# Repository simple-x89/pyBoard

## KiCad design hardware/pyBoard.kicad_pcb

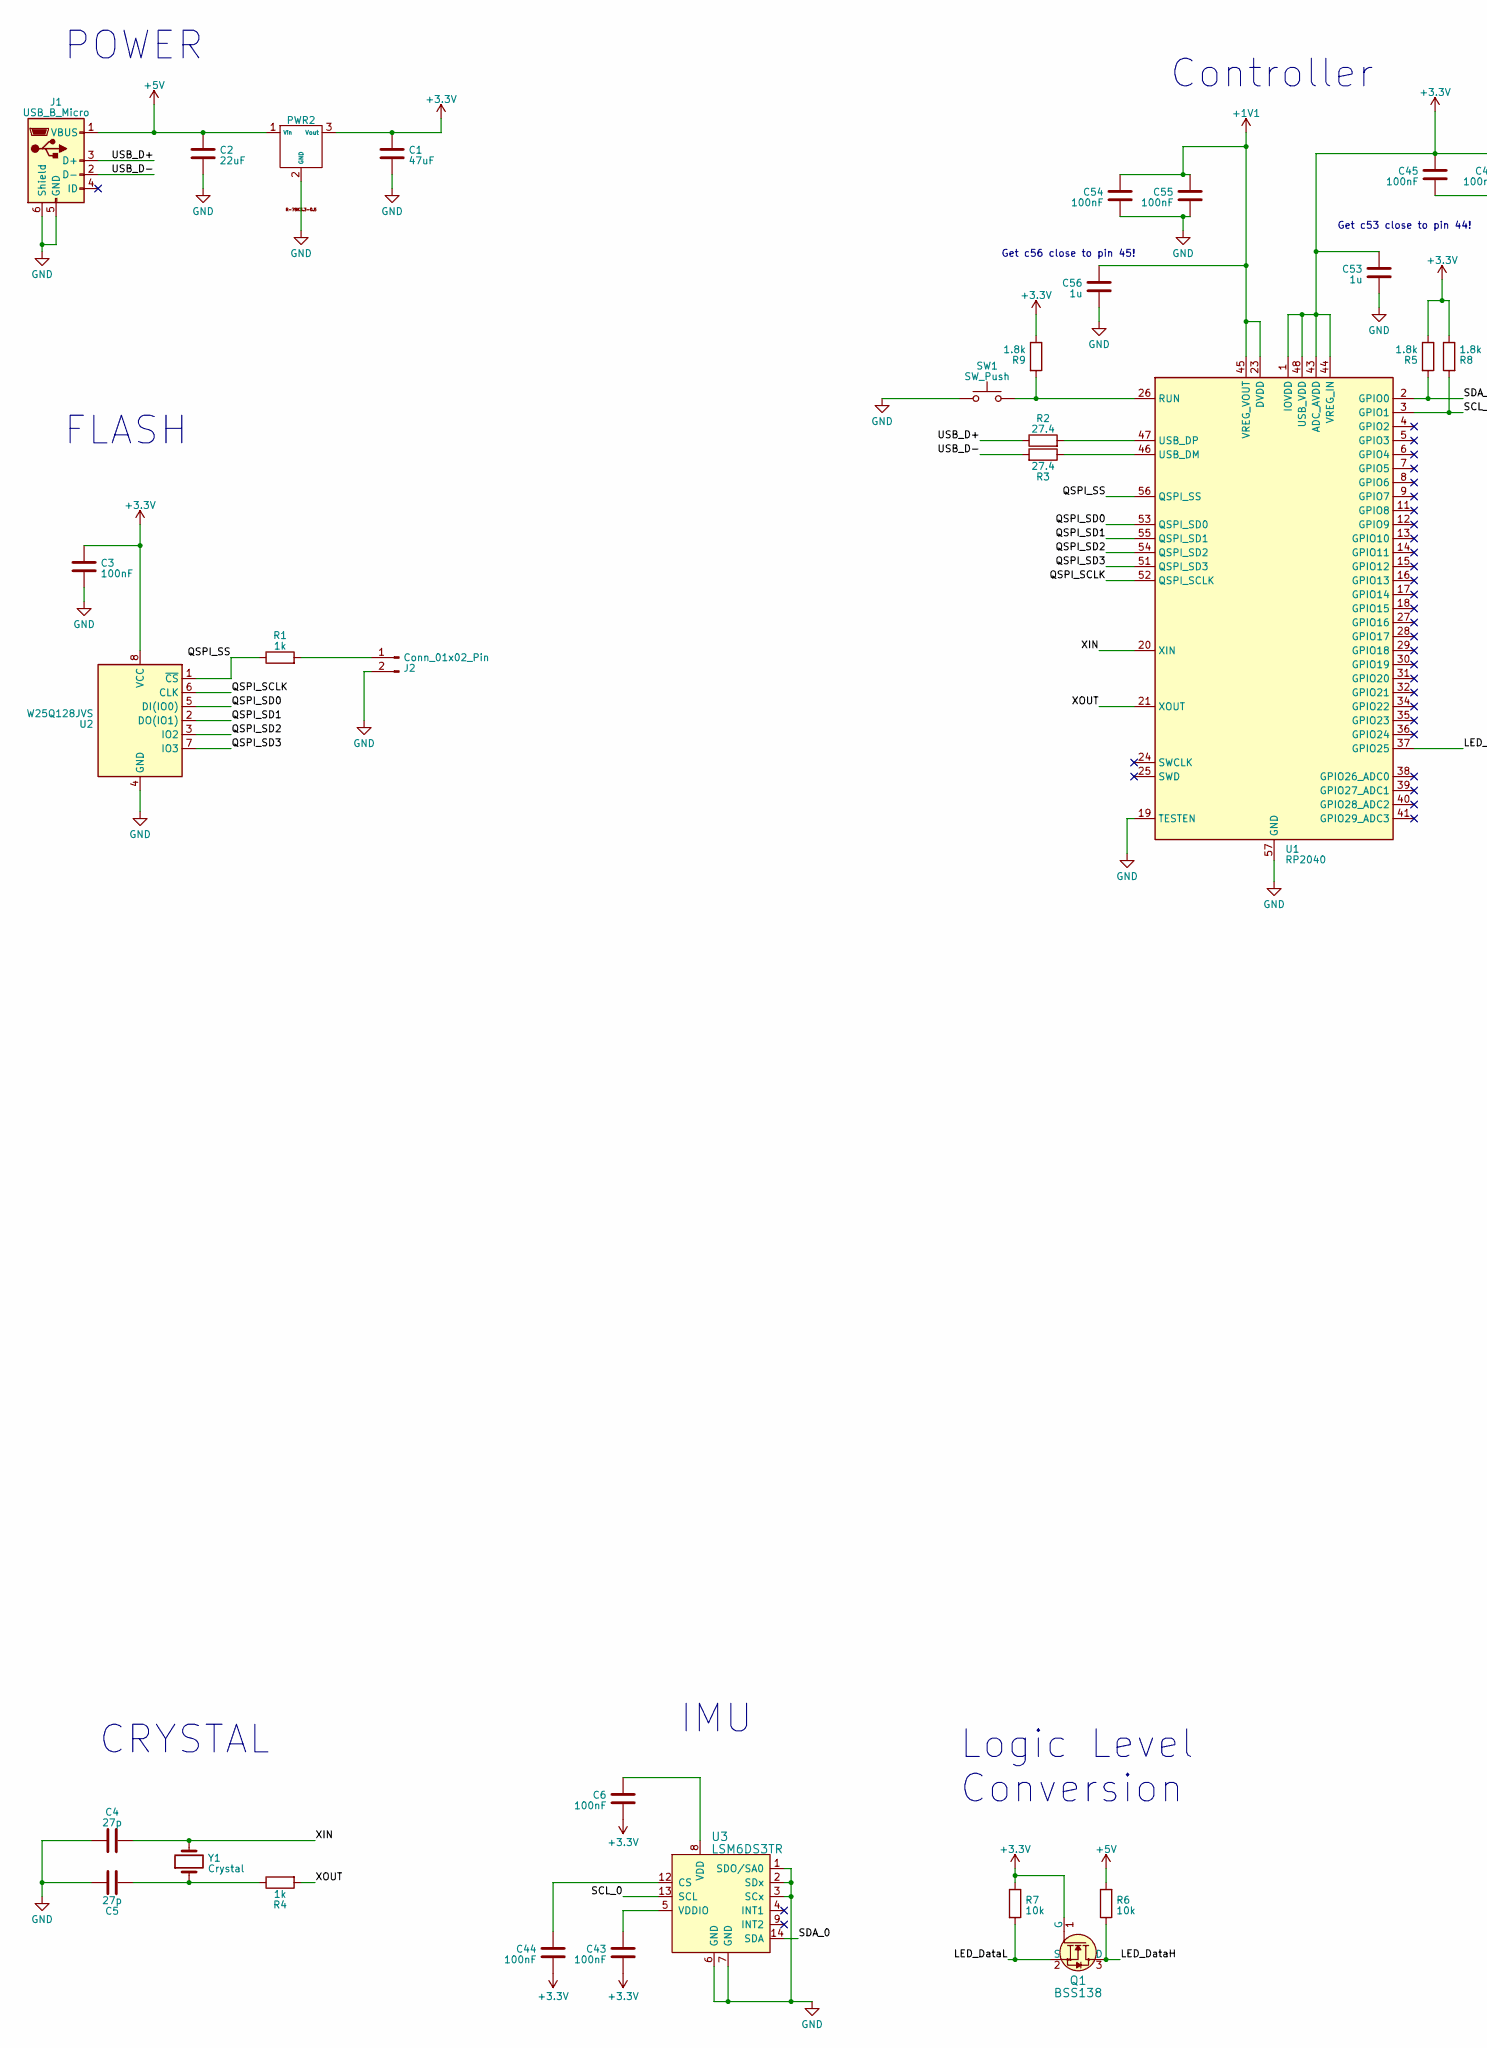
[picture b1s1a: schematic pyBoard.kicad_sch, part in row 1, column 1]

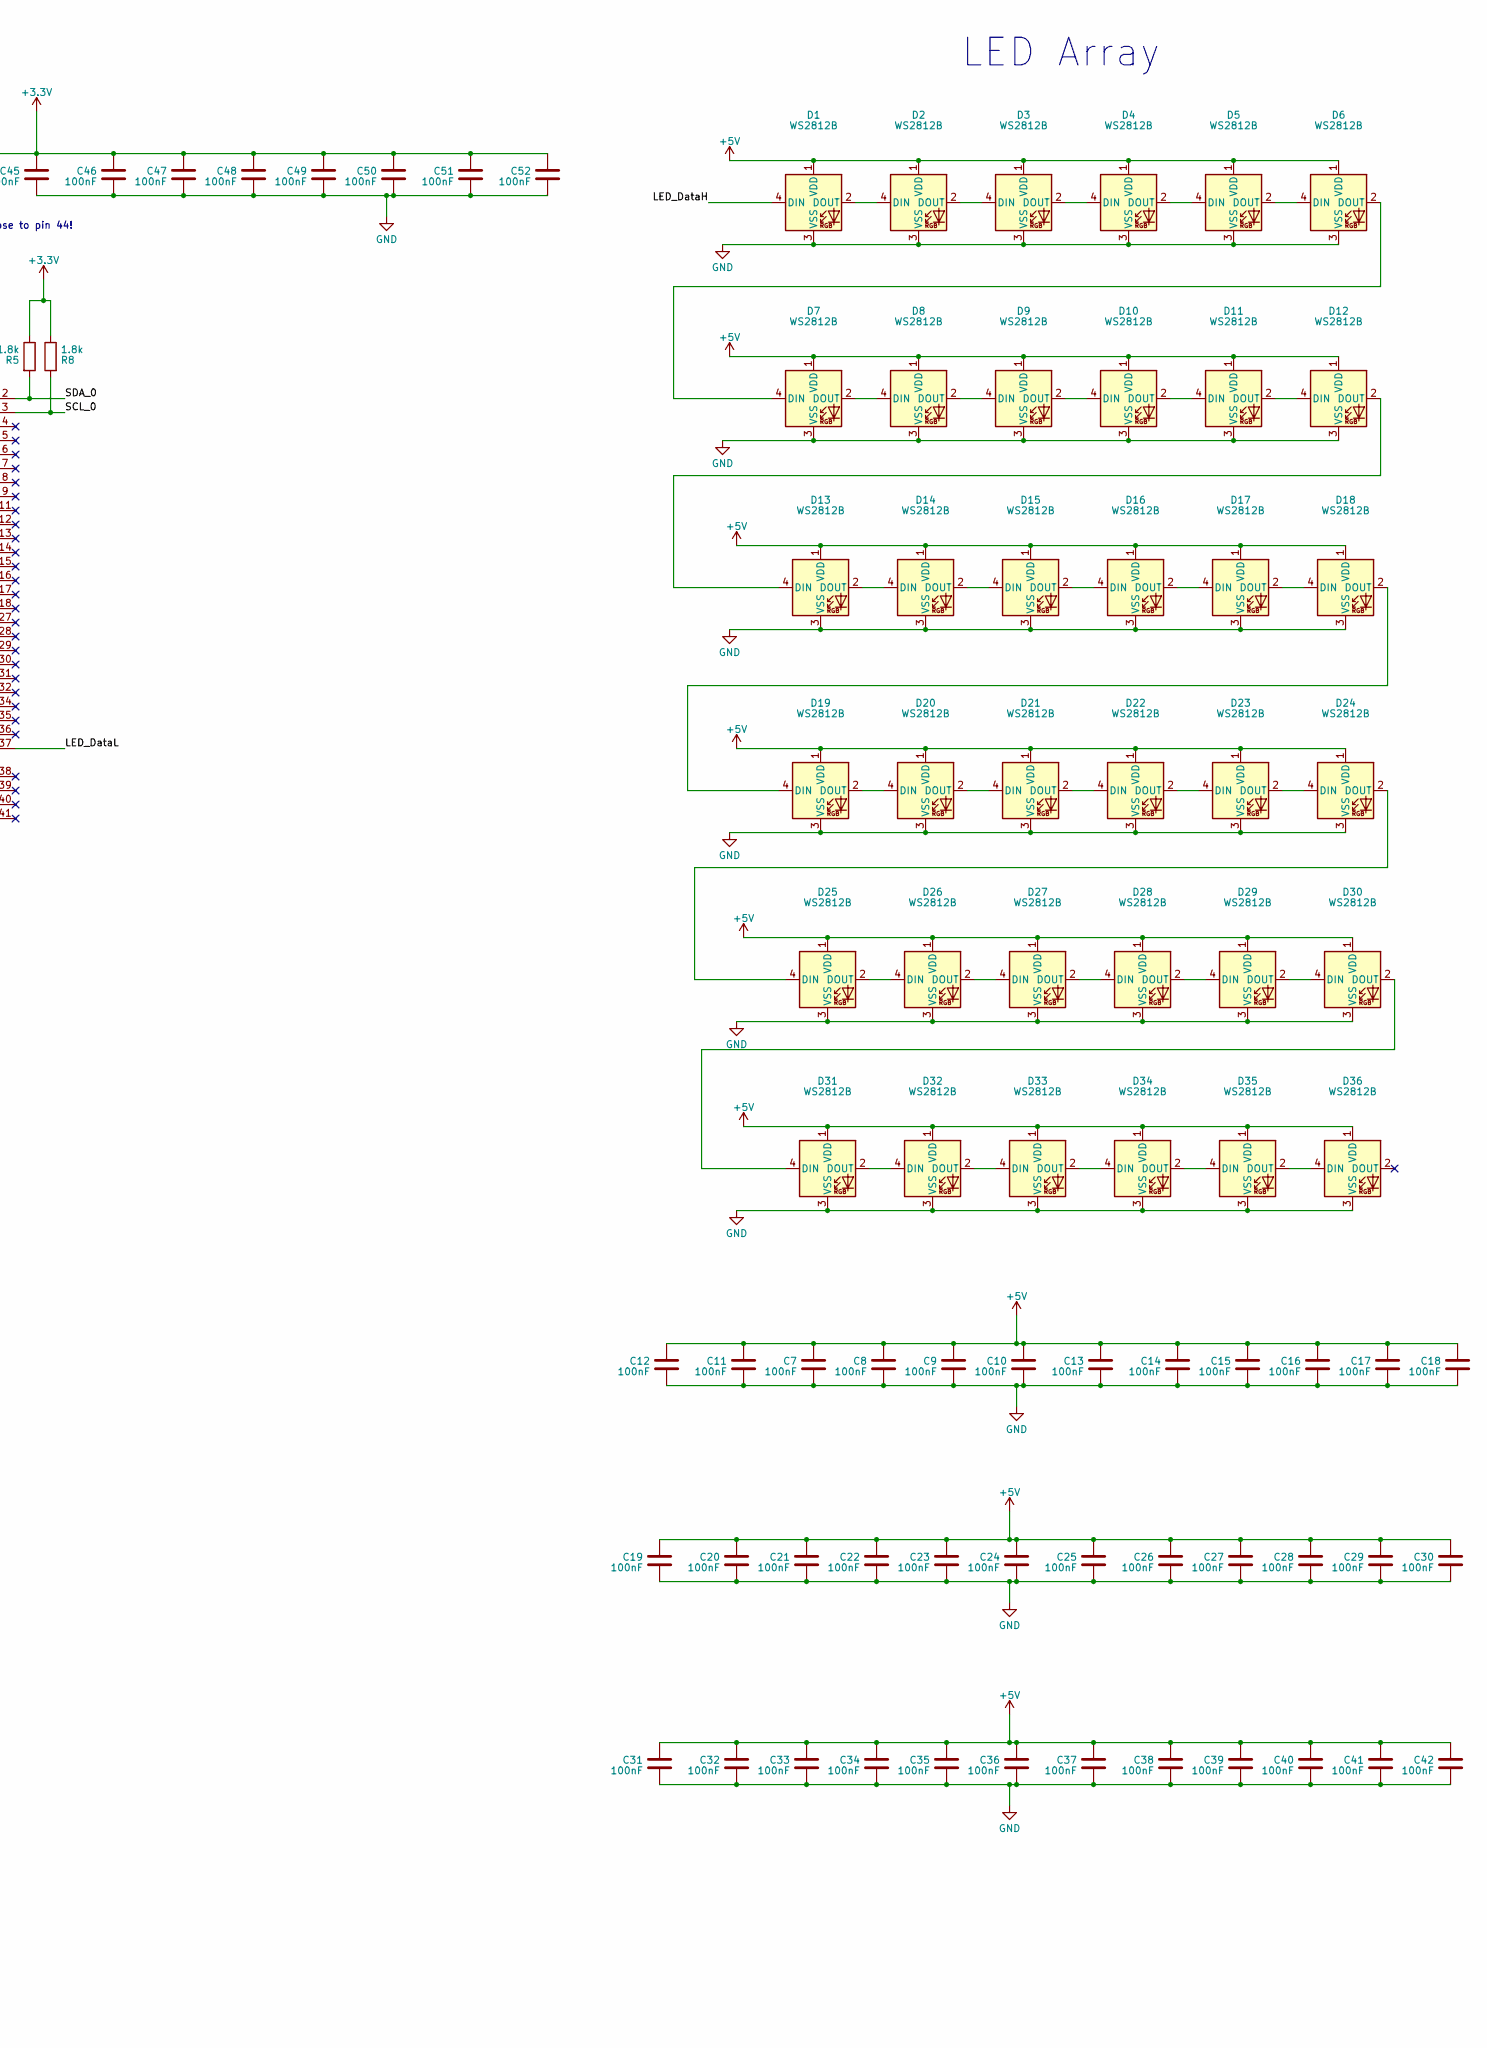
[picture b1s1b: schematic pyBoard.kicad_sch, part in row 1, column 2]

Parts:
C1: 47uF; C_0603_1608Metric
C2: 22uF; C_0603_1608Metric
C3, C6, C7, C8, C9, C10, C11, C12, C13, C14, C15, C16, C17, C18, C19, C20, C21, C22, C23, C24, C25, C26, C27, C28, C29, C30, C31, C32, C33, C34, C35, C36, C37, C38, C39, C40, C41, C42, C43, C44, C45, C46, C47, C48, C49, C50, C51, C52, C54, C55: 100nF; C_0603_1608Metric
C4, C5: 27p; C_0603_1608Metric
C53, C56: 1u; C_0603_1608Metric
D1, D2, D3, D4, D5, D6, D7, D8, D9, D10, D11, D12, D13, D14, D15, D16, D17, D18, D19, D20, D21, D22, D23, D24, D25, D26, D27, D28, D29, D30, D31, D32, D33, D34, D35, D36: WS2812B; LED_WS2812B-2020_PLCC4_2.0x2.0mm
J1: USB_B_Micro; USB_Mini_B_Female_690-005-299-043
J2: Conn_01x02_Pin; PinHeader_1x02_P2.54mm_Vertical
PWR2: R-78K3.3-0.5; PinHeader_1x03_P2.54mm_Vertical
Q1: BSS138; SOT-23-3; MPN BSS138; Digi-Key_PN BSS138CT-ND
R1, R4: 1k; R_0603_1608Metric_Pad0.98x0.95mm_HandSolder
R2, R3: 27.4; R_0603_1608Metric_Pad0.98x0.95mm_HandSolder
R5, R8, R9: 1.8k; R_0603_1608Metric_Pad0.98x0.95mm_HandSolder
R6, R7: 10k; R_0603_1608Metric_Pad0.98x0.95mm_HandSolder
SW1: SW_Push; SW_SPST_B3S-1000
U1: RP2040; QFN-56-1EP_7x7mm_P0.4mm_EP3.2x3.2mm
U2: W25Q128JVS; SOIC-8_5.23x5.23mm_P1.27mm
U3: LSM6DS3TR; LGA-14L_2.5x3mm__LSM6DS3; MPN LSM6DS3TR; Digi-Key_PN 497-15383-1-ND
Y1: Crystal; Crystal_SMD_HC49-SD

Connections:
+1V1: C54.1, C55.1, C56.1, U1.23 (DVDD), U1.45 (VREG_VOUT), U1.50 (DVDD)
+3.3V: C1.1, C3.1, C6.2, C43.2, C44.2, C45.1, C46.1, C47.1, C48.1, C49.1, C50.1, C51.1, C52.1, C53.1, PWR2.3 (Vout), Q1.1 (G), R5.1, R7.1, R8.1, R9.1, U1.1 (IOVDD), U1.10 (IOVDD), U1.22 (IOVDD), U1.33 (IOVDD), U1.42 (IOVDD), U1.43 (ADC_AVDD), U1.44 (VREG_IN), U1.48 (USB_VDD), U1.49 (IOVDD), U2.8 (VCC)
+5V: C2.1, C7.1, C8.1, C9.1, C10.1, C11.1, C12.1, C13.1, C14.1, C15.1, C16.1, C17.1, C18.1, C19.1, C20.1, C21.1, C22.1, C23.1, C24.1, C25.1, C26.1, C27.1, C28.1, C29.1, C30.1, C31.1, C32.1, C33.1, C34.1, C35.1, C36.1, C37.1, C38.1, C39.1, C40.1, C41.1, C42.1, D1.1 (VDD), D2.1 (VDD), D3.1 (VDD), D4.1 (VDD), D5.1 (VDD), D6.1 (VDD), D7.1 (VDD), D8.1 (VDD), D9.1 (VDD), D10.1 (VDD), D11.1 (VDD), D12.1 (VDD), D13.1 (VDD), D14.1 (VDD), D15.1 (VDD), D16.1 (VDD), D17.1 (VDD), D18.1 (VDD), D19.1 (VDD), D20.1 (VDD), D21.1 (VDD), D22.1 (VDD), D23.1 (VDD), D24.1 (VDD), D25.1 (VDD), D26.1 (VDD), D27.1 (VDD), D28.1 (VDD), D29.1 (VDD), D30.1 (VDD), D31.1 (VDD), D32.1 (VDD), D33.1 (VDD), D34.1 (VDD), D35.1 (VDD), D36.1 (VDD), J1.1 (VBUS), PWR2.1 (Vin), R6.2
/LED_DataH: D1.4 (DIN), Q1.3 (D), R6.1
/LED_DataL: Q1.2 (S), R7.2, U1.37 (GPIO25)
/QSPI_SCLK: U1.52 (QSPI_SCLK), U2.6 (CLK)
/QSPI_SD0: U1.53 (QSPI_SD0), U2.5 (DI(IO0))
/QSPI_SD1: U1.55 (QSPI_SD1), U2.2 (DO(IO1))
/QSPI_SD2: U1.54 (QSPI_SD2), U2.3 (IO2)
/QSPI_SD3: U1.51 (QSPI_SD3), U2.7 (IO3)
/QSPI_SS: R1.1, U1.56 (QSPI_SS), U2.1 (~CS)
/SCL_0: R8.2, U1.3 (GPIO1), U3.13 (SCL)
/SDA_0: R5.2, U1.2 (GPIO0), U3.14 (SDA)
/USB_D+: J1.3 (D+), R2.1
/USB_D-: J1.2 (D-), R3.2
/XIN: C4.2, U1.20 (XIN), Y1.2
/XOUT: R4.2, U1.21 (XOUT)
GND: C1.2, C2.2, C3.2, C4.1, C5.1, C7.2, C8.2, C9.2, C10.2, C11.2, C12.2, C13.2, C14.2, C15.2, C16.2, C17.2, C18.2, C19.2, C20.2, C21.2, C22.2, C23.2, C24.2, C25.2, C26.2, C27.2, C28.2, C29.2, C30.2, C31.2, C32.2, C33.2, C34.2, C35.2, C36.2, C37.2, C38.2, C39.2, C40.2, C41.2, C42.2, C45.2, C46.2, C47.2, C48.2, C49.2, C50.2, C51.2, C52.2, C53.2, C54.2, C55.2, C56.2, D1.3 (VSS), D2.3 (VSS), D3.3 (VSS), D4.3 (VSS), D5.3 (VSS), D6.3 (VSS), D7.3 (VSS), D8.3 (VSS), D9.3 (VSS), D10.3 (VSS), D11.3 (VSS), D12.3 (VSS), D13.3 (VSS), D14.3 (VSS), D15.3 (VSS), D16.3 (VSS), D17.3 (VSS), D18.3 (VSS), D19.3 (VSS), D20.3 (VSS), D21.3 (VSS), D22.3 (VSS), D23.3 (VSS), D24.3 (VSS), D25.3 (VSS), D26.3 (VSS), D27.3 (VSS), D28.3 (VSS), D29.3 (VSS), D30.3 (VSS), D31.3 (VSS), D32.3 (VSS), D33.3 (VSS), D34.3 (VSS), D35.3 (VSS), D36.3 (VSS), J1.5 (GND), J1.6 (Shield), J2.2, PWR2.2 (GND), SW1.1, U1.19 (TESTEN), U1.57 (GND), U2.4 (GND), U3.1 (SDO/SA0), U3.2 (SDx), U3.3 (SCx), U3.6 (GND), U3.7 (GND)
unnamed: C5.2, R4.1, Y1.1
unnamed: D1.2 (DOUT), D2.4 (DIN)
unnamed: D2.2 (DOUT), D3.4 (DIN)
unnamed: D3.2 (DOUT), D4.4 (DIN)
unnamed: D4.2 (DOUT), D5.4 (DIN)
unnamed: D5.2 (DOUT), D6.4 (DIN)
unnamed: D6.2 (DOUT), D7.4 (DIN)
unnamed: D7.2 (DOUT), D8.4 (DIN)
unnamed: D8.2 (DOUT), D9.4 (DIN)
unnamed: D9.2 (DOUT), D10.4 (DIN)
unnamed: D10.2 (DOUT), D11.4 (DIN)
unnamed: D11.2 (DOUT), D12.4 (DIN)
unnamed: D12.2 (DOUT), D13.4 (DIN)
unnamed: D13.2 (DOUT), D14.4 (DIN)
unnamed: D14.2 (DOUT), D15.4 (DIN)
unnamed: D15.2 (DOUT), D16.4 (DIN)
unnamed: D16.2 (DOUT), D17.4 (DIN)
unnamed: D17.2 (DOUT), D18.4 (DIN)
unnamed: D18.2 (DOUT), D19.4 (DIN)
unnamed: D19.2 (DOUT), D20.4 (DIN)
unnamed: D20.2 (DOUT), D21.4 (DIN)
unnamed: D21.2 (DOUT), D22.4 (DIN)
unnamed: D22.2 (DOUT), D23.4 (DIN)
unnamed: D23.2 (DOUT), D24.4 (DIN)
unnamed: D24.2 (DOUT), D25.4 (DIN)
unnamed: D25.2 (DOUT), D26.4 (DIN)
unnamed: D26.2 (DOUT), D27.4 (DIN)
unnamed: D27.2 (DOUT), D28.4 (DIN)
unnamed: D28.2 (DOUT), D29.4 (DIN)
unnamed: D29.2 (DOUT), D30.4 (DIN)
unnamed: D30.2 (DOUT), D31.4 (DIN)
unnamed: D31.2 (DOUT), D32.4 (DIN)
unnamed: D32.2 (DOUT), D33.4 (DIN)
unnamed: D33.2 (DOUT), D34.4 (DIN)
unnamed: D34.2 (DOUT), D35.4 (DIN)
unnamed: D35.2 (DOUT), D36.4 (DIN)
unnamed: J2.1, R1.2
unnamed: R9.2, SW1.2, U1.26 (RUN)
unnamed: R3.1, U1.46 (USB_DM)
unnamed: R2.2, U1.47 (USB_DP)
unnamed: C44.1, U3.12 (CS)
unnamed: C6.1, U3.8 (VDD)
unnamed: C43.1, U3.5 (VDDIO)

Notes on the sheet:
POWER
Logic Level Conversion
Get c53 close to pin 44!
Get c56 close to pin 45!
IMU
CRYSTAL
Controller
LED Array
FLASH

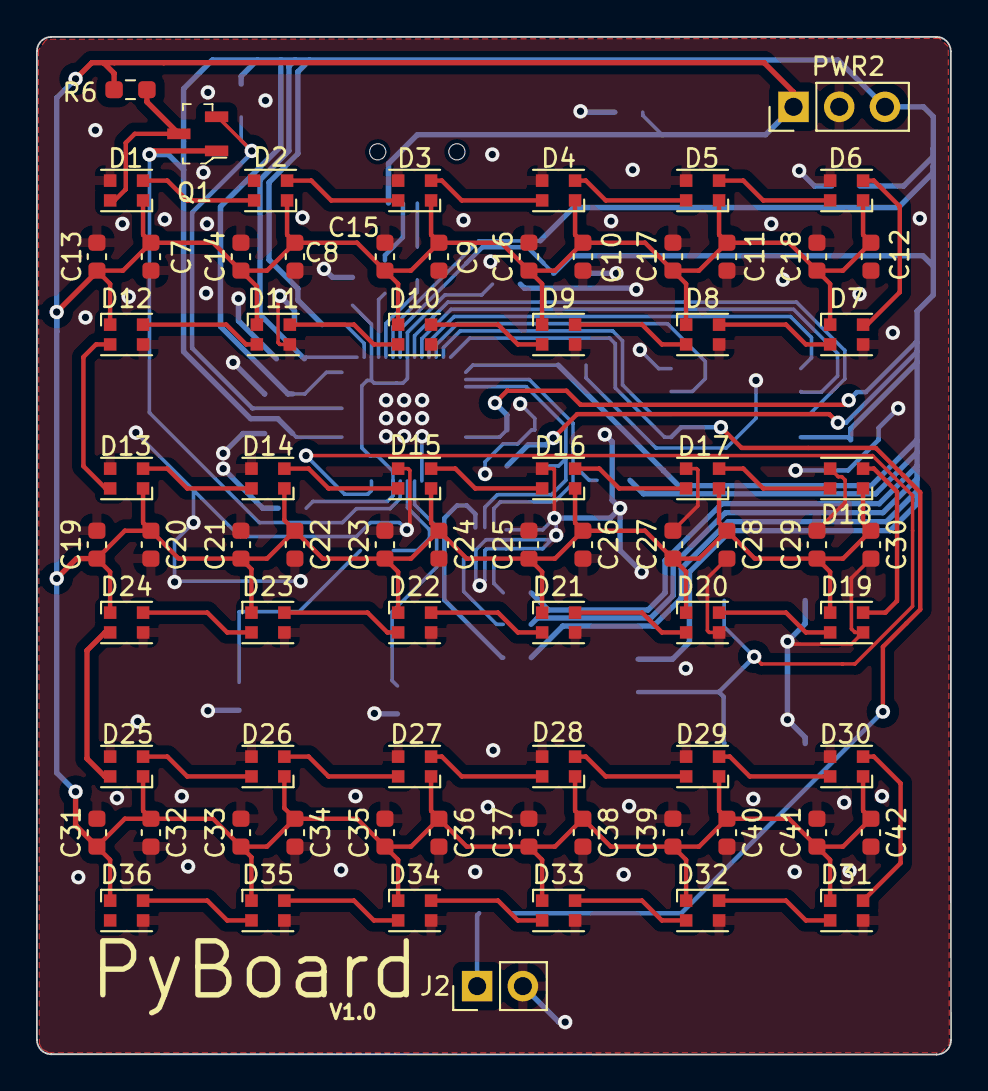
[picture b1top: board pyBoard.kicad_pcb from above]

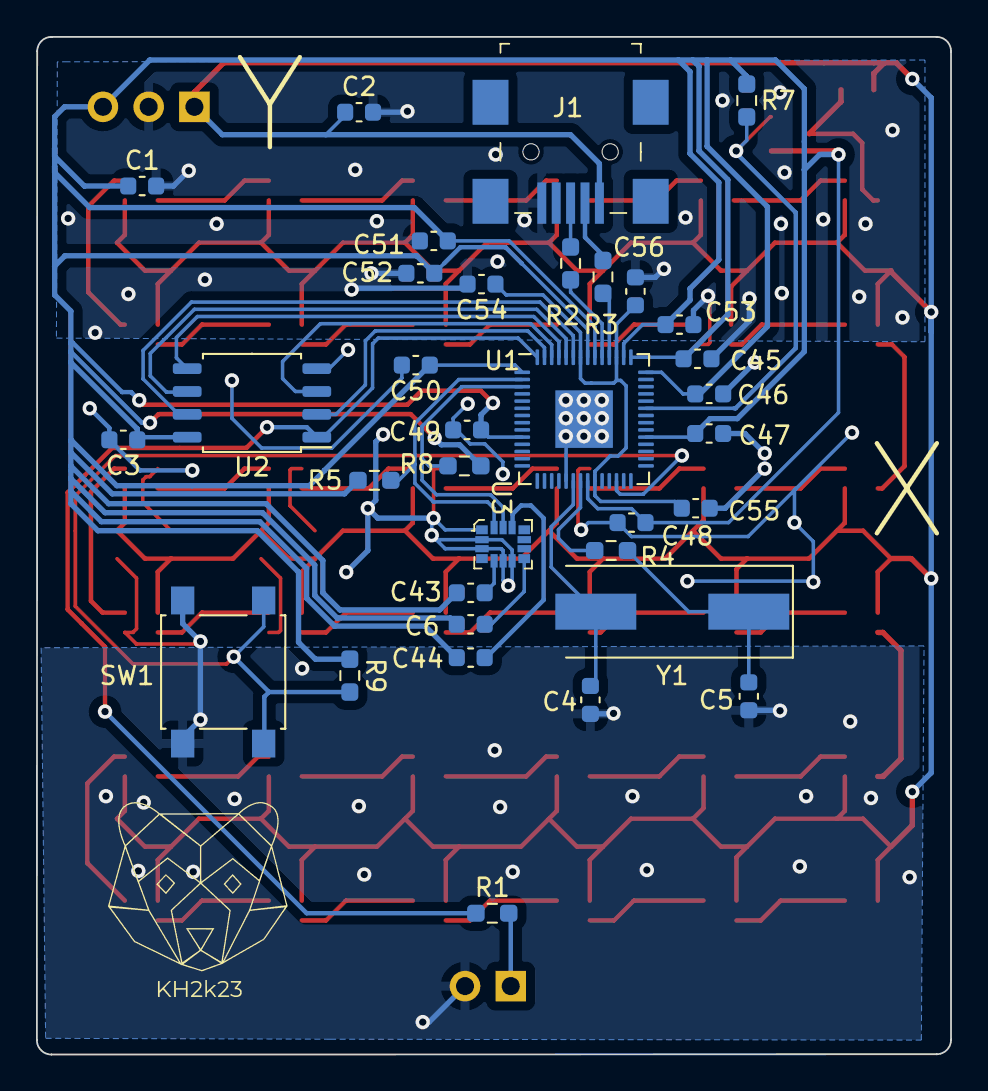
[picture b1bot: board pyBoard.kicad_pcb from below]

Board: 2 copper layers, 50.8 x 56.5 mm, 110 parts (34 on the bottom side), 61 nets.

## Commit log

2023-03-12 hardware design and related media
2023-03-22 Presentation and software demos added
